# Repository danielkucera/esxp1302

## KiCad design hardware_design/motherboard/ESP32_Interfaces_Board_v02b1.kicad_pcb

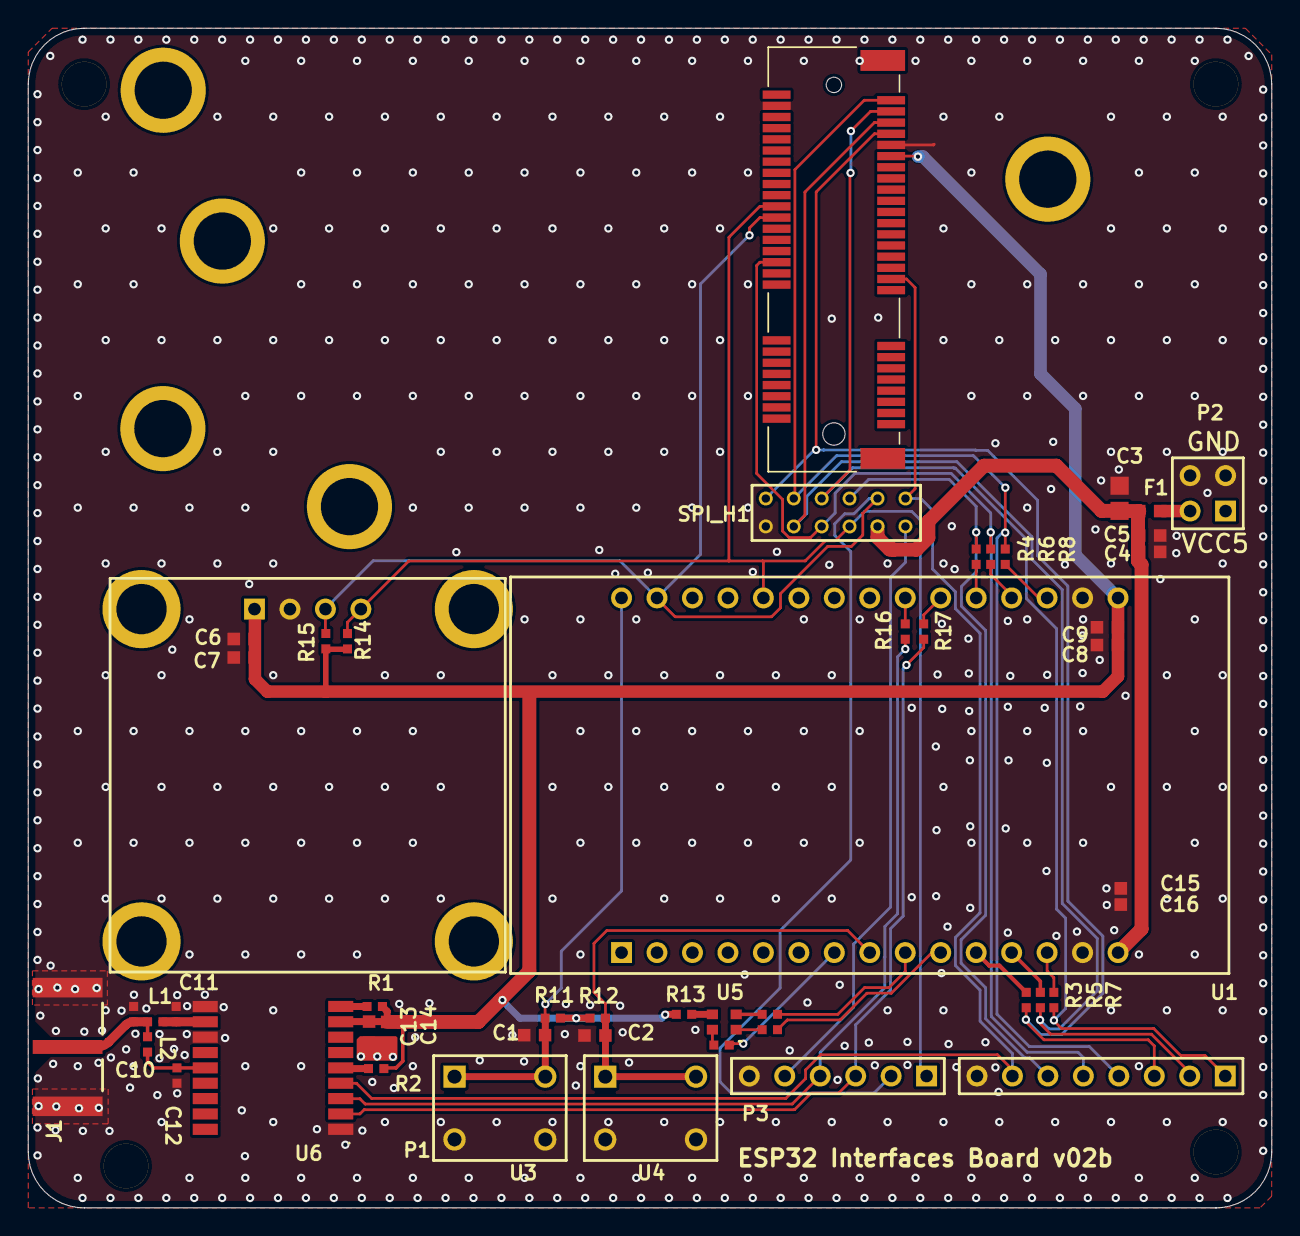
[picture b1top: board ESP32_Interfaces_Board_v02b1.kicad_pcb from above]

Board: 2 copper layers, 89.1 x 84.5 mm, 53 parts (0 on the bottom side), 38 nets.

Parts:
C1, C2, C4, C5, C6, C7, C8, C9, C13, C14, C15, C16: Cap; rlc_603_smd
C3: Cap; rlc_805_smd
C10, C11, C12: Cap; rlc_402_smd
F1: Ferrite beads; rlc_603_smd
J1: 32K145-400L5; ROS-32K145-400L5_V
L1, L2: Inductor; rlc_402_smd
P1: Header 8; HDR1X8
P2: Header 2X2; HDR2X2
P3: Header 6; HDR1X6
R1, R2, R3, R4, R5, R6, R7, R8, R9, R10, R11, R12, R13, R14, R15, R16, R17, R18: Resistor; rlc_402_smd
S1: GW_SHAPE
SCREW-1, SCREW-3: Logo symbol; screw-M3
SCREW-2, SCREW-4: Logo symbol; SCREW-M3
SPI_H1: Header 6X2; header_6_2_2.0
U1: ESP32_Devkit_V1; ESP32-DOIT-30
U2: JMD0.96-12864; JMD0.96_12864
U3: Button1; TACT SWITCH_8HA-A-S1-01 - DUPLICATE
U4: Button2; TACT SWITCH_8HA-A-S1-01 - DUPLICATE
U5: FM-B2020RGBA-HG; RGB_2020
U6: ATGM336H-GPS; ATGM336H

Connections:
1PPS: P1.7, SPI_H1.12, U6.4
EN-Pwr: P1.6, R4.2, SPI_H1.8
GND: C1.2, C2.2, C3.1, C4.1, C5.1, C6.2, C7.2, C8.2, C9.2, C10.2, C11.1, C12.1, C13.1, C14.1, C15.2, C16.2, J1.MP, P1.8, P2.3, P2.4, P3.6, SPI_H1.1, U1.14, U1.17, U2.2, U3.3, U3.4, U4.3, U4.4, U6.1, U6.10, U6.12
GPS_NRST: P3.5, SPI_H1.11
LED_Blue: R10.2, U1.7
LED_Green: R9.1, U1.9
LED_Red: R18.1, U1.10
MISO: P1.2, R5.1, SPI_H1.3
MOSI: P1.1, R7.1, SPI_H1.6
NRESET: P1.5, R6.2, SPI_H1.5
NSS: P1.4, R8.2, SPI_H1.4
NetC10_1: C10.1, J1.1, L1.1, L2.1
NetC11_2: C11.2, L1.2, U6.11
NetC12_2: C12.2, L2.2, U6.14
NetF1_1: F1.1, P2.2
NetR1_1: R1.1, U6.9
NetR2_1: R2.1, U6.5
NetR3_2: R3.2, U1.11
NetR4_1: R4.1, U1.20
NetR5_2: R5.2, U1.12
NetR6_1: R6.1, U1.19
NetR7_2: R7.2, U1.13
NetR8_1: R8.1, U1.18
NetR9_2: R9.2, U5.4
NetR10_1: R10.1, U5.2
NetR13_1: R13.1, U5.3
NetR16_1: R16.1, U1.22
NetR17_1: R17.1, U1.21
NetR18_2: R18.2, U5.1
RXD: P3.3, R17.2, U6.2
SCK: P1.3, R3.1, SPI_H1.2
SCL: P3.2, R15.2, SPI_H1.10, U1.29, U2.3
SDA: P3.1, R14.2, SPI_H1.7, U1.26, U2.4
TXD: P3.4, R16.2, U6.3
User_Button1: C1.1, R11.2, U1.30, U3.1, U3.2
User_Button2: C2.1, R12.2, U1.8, U4.1, U4.2
VCC3V3: C6.1, C7.1, C8.1, C9.1, C13.2, C14.2, R1.2, R2.2, R11.1, R12.1, R13.2, R14.1, R15.1, U1.16, U2.1, U6.8
VCC5V: C3.2, C4.2, C5.2, C15.1, C16.1, F1.2, SPI_H1.9, U1.15

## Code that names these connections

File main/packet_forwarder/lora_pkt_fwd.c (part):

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
void Init_Led( void )
{
    gpio_pad_select_gpio( LED_BLUE_GPIO );
    gpio_pad_select_gpio( LED_GREEN_GPIO );
    gpio_pad_select_gpio( LED_RED_GPIO );
    gpio_set_direction( LED_BLUE_GPIO, GPIO_MODE_OUTPUT );
    gpio_set_direction( LED_GREEN_GPIO, GPIO_MODE_OUTPUT );
    gpio_set_direction( LED_RED_GPIO, GPIO_MODE_OUTPUT );
    gpio_set_level( LED_BLUE_GPIO, 1 );   // Default state
    gpio_set_level( LED_GREEN_GPIO, 1 );   // Default state
    gpio_set_level( LED_RED_GPIO, 1 );   // Default state
}

static int parse_SX130x_configuration(const char * conf_array) {
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
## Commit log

2023-12-18 KiCad Altium import
2024-01-03 pcie routed
2024-02-03 remove pcie connector reference
2024-06-16 wip: separate networking
2024-06-21 Make code work better when some GPIOs missing
2025-04-18 forgotten network files

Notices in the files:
main/packet_forwarder/lora_pkt_fwd.c:
(C)2019 Semtech
License: Revised BSD License, see LICENSE.TXT file include in the project
